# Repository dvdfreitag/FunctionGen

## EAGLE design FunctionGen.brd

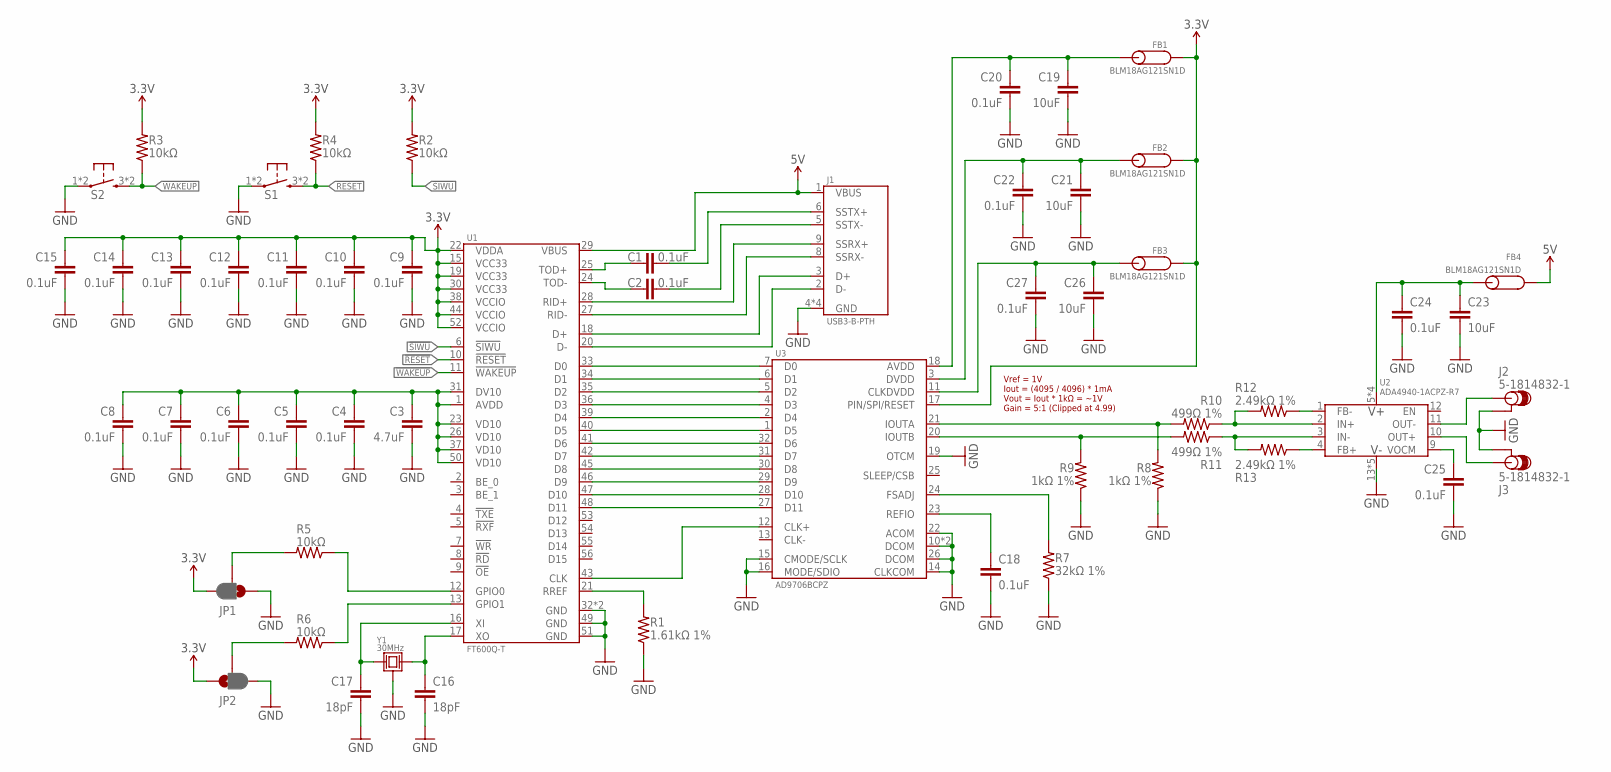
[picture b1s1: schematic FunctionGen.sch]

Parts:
C1, C2, C4, C5, C6, C7, C8, C9, C10, C11, C12, C13, C14, C15, C18, C20, C22, C24, C25, C27: 0.1uF; 0603-CAP
C3: 4.7uF; 0603-CAP
C16, C17: 18pF; 0603-CAP
C19, C21, C23, C26: 10uF; 0603-CAP
FB1, FB2, FB3, FB4: BLM18AG121SN1D; 0603-FERRITE
J1: USB3-B-PTH; GSB4211311WEU
J2, J3: 5-1814832-1; SMA-PTH
JP1, JP2: JUMPER-PAD-3-2OF3_NC_BY_PASTE; PAD-JUMPER-3-2OF3_NC_BY_PASTE_YES_SILK_FULL_BOX
R1: 1.61kΩ 1%; 0603-CAP
R2, R3, R4, R5, R6: 10kΩ; 0603-CAP
R7: 32kΩ 1%; 0603-CAP
R8, R9: 1kΩ 1%; 0603-CAP
R10, R11: 499Ω 1%; 0603-CAP
R12, R13: 2.49kΩ 1%; 0603-CAP
S1, S2: TACTILE-SMD3; FSM4JSMA
U1: FT600Q-T; VQFN-56-7MM
U2: ADA4940-1ACPZ-R7; VQFN-16-3MM
U3: AD9706BCPZ; VQFN-32-5MM
Y1: 30MHz; FA-238

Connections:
3.3V: C9.1, C10.1, C11.1, C12.1, C13.1, C14.1, C15.1, FB1.P$1, FB2.P$1, FB3.P$1, JP1.3, JP2.1, R2.2, R3.2, R4.2, U1.15 (VCC33), U1.19 (VCC33), U1.22 (VDDA), U1.30 (VCC33), U1.38 (VCCIO), U1.44 (VCCIO), U1.52 (VCCIO), U3.17 (PIN/SPI/RESET)
5V: FB4.P$1, J1.1 (VBUS), U1.29 (VBUS)
!RESET: R4.1, S1.3, S1.4 (3), U1.10 (!RESET)
!SIWU: R2.1, U1.6 (!SIWU)
!WAKEUP: R3.1, S2.3, S2.4 (3), U1.11 (!WAKEUP)
CLK: U1.43 (CLK), U3.12 (CLK+)
D0: U1.33 (D0), U3.7 (D0)
D1: U1.34 (D1), U3.6 (D1)
D2: U1.35 (D2), U3.5 (D2)
D3: U1.36 (D3), U3.4 (D3)
D4: U1.39 (D4), U3.2 (D4)
D5: U1.40 (D5), U3.1 (D5)
D6: U1.41 (D6), U3.32 (D6)
D7: U1.42 (D7), U3.31 (D7)
D8: U1.45 (D8), U3.30 (D8)
D9: U1.46 (D9), U3.29 (D9)
D10: U1.47 (D10), U3.28 (D10)
D11: U1.48 (D11), U3.27 (D11)
D_N: J1.2 (D-), U1.20 (D-)
D_P: J1.3 (D+), U1.18 (D+)
GND: C3.2, C4.2, C5.2, C6.2, C7.2, C8.2, C9.2, C10.2, C11.2, C12.2, C13.2, C14.2, C15.2, C16.2, C17.2, C18.2, C19.2, C20.2, C21.2, C22.2, C23.2, C24.2, C25.2, C26.2, C27.2, J1.4 (GND), J1.7 (GND), J1.P$10 (GND), J1.P$11 (GND), J2.P$1 (GND), J2.P$2 (GND), J2.P$3 (GND), J2.P$4 (GND), J3.P$1 (GND), J3.P$2 (GND), J3.P$3 (GND), J3.P$4 (GND), JP1.1, JP2.3, R1.1, R7.1, R8.1, R9.1, S1.1, S1.2 (1), S2.1, S2.2 (1), U1.32 (GND), U1.49 (GND), U1.51 (GND), U1.PAD (GND), U2.13 (VS-), U2.14 (VS-), U2.15 (VS-), U2.16 (VS-), U2.PAD (VS-), U3.10 (DCOM), U3.14 (CLKCOM), U3.15 (CMODE/SCLK), U3.16 (MODE/SDIO), U3.19 (OTCM), U3.22 (ACOM), U3.26 (DCOM), U3.PAD (DCOM), Y1.2 (GND), Y1.4 (GND)
GPIO0: R5.1, U1.12 (GPIO0)
GPIO1: R6.1, U1.13 (GPIO1)
unnamed: C3.1, C4.1, C5.1, C6.1, C7.1, C8.1, U1.1 (AVDD), U1.23 (VD10), U1.26 (VD10), U1.31 (DV10), U1.37 (VD10), U1.50 (VD10)
unnamed: R1.2, U1.21 (RREF)
unnamed: C17.1, U1.16 (XI), Y1.1
unnamed: C16.1, U1.17 (XO), Y1.3 (2)
unnamed: JP1.2, R5.2
unnamed: JP2.2, R6.2
unnamed: C18.1, U3.23 (REFIO)
unnamed: R7.2, U3.24 (FSADJ)
unnamed: C19.1, C20.1, FB1.P$2, U3.18 (AVDD)
unnamed: C21.1, C22.1, FB2.P$2, U3.3 (DVDD)
unnamed: C26.1, C27.1, FB3.P$2, U3.11 (CLKDVDD)
unnamed: C23.1, C24.1, FB4.P$2, U2.5 (VS+), U2.6 (VS+), U2.7 (VS+), U2.8 (VS+)
unnamed: C25.1, U2.9 (VOCM)
unnamed: R13.1, U2.4 (FB+)
unnamed: R12.1, U2.1 (FB-)
unnamed: R10.1, R12.2, U2.2 (IN+)
unnamed: R11.1, R13.2, U2.3 (IN-)
unnamed: R9.2, R11.2, U3.20 (IOUTB)
unnamed: R8.2, R10.2, U3.21 (IOUTA)
unnamed: J3.SIGNAL, U2.10 (OUT+)
unnamed: J2.SIGNAL, U2.11 (OUT-)
R_N: J1.8 (SSRX-), U1.27 (RID-)
R_P: J1.9 (SSRX+), U1.28 (RID+)
T_N: C2.2, J1.5 (SSTX-)
T_P: C1.2, J1.6 (SSTX+)
_T_N: C2.1, U1.24 (TOD-)
_T_P: C1.1, U1.25 (TOD+)

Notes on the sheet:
Vref = 1V Iout = (4095 / 4096) * 1mA Vout = Iout * 1kΩ = ~1V Gain = 5:1 (Clipped at 4.99)

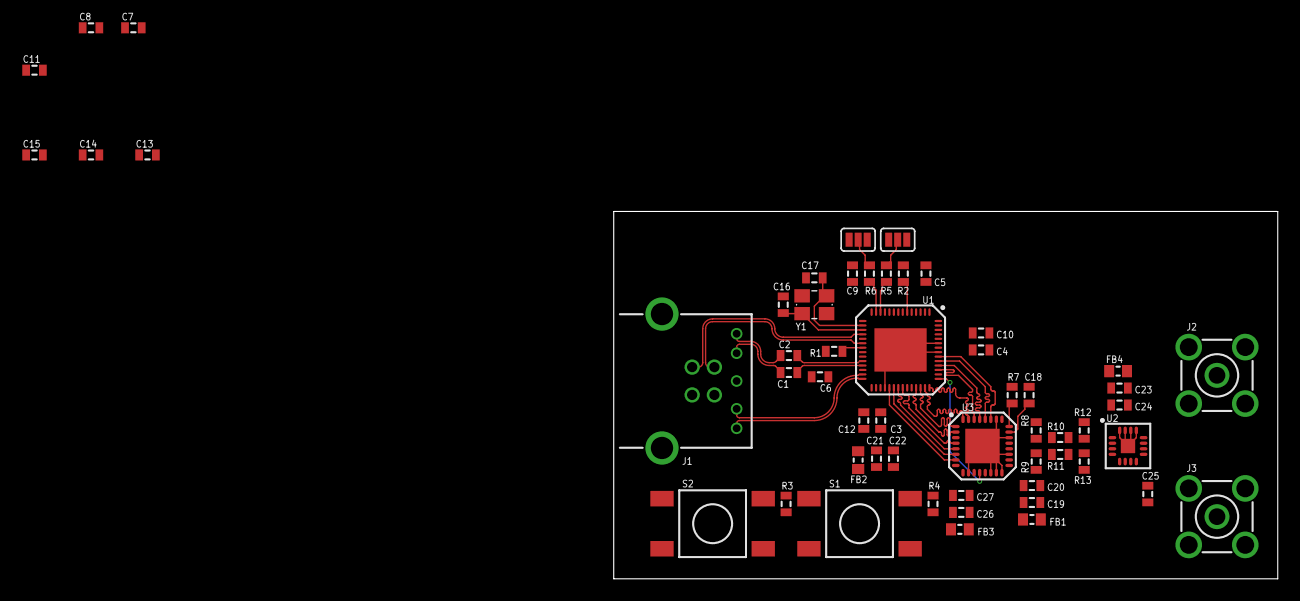
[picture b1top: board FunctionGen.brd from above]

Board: 4 copper layers, 59.7 x 33.0 mm, 55 parts (0 on the bottom side), 50 nets.

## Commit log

2016-08-11 Initial commit
    Layout still needs to be finished
2016-08-11 Create LICENSE

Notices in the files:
parts and their libraries:
SparkFun-Passives: Licensing: Creative Commons ShareAlike 4.0 International - https://creativecommons.org/licenses/by-sa/4.0
